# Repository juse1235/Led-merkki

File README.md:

# Salama
Sikin led salamaan ja Otitin led merkkiin koodi, piirilevy ja ohjeet

## Piirilevyt
### Mistä salama koostuu ja miten se toimii
Salaman mikrokontrolleri (mcu) ohjaa ledejä sytyttäen niitä yksi kerrallaan hyvin lyhyeksi aikaa.
Ledejä on 32 ja niille on 110 ohm etuvastukset.
Salamassa on myös 5v regulaattori joka pienentää 9v paristosta saatavan jännitteen viiteen volttiin.
Regulaattori vaatii toimiakseen kondensaattorit molemmille puolilleen.
Levyyn on myös suunniteltu kytkin, jolla voisi vaikka sammuttaa laitteen tai toimittaa muuta toiminnallisuutta, mutta näitä ei ole koodissa toteutettu vielä.
Kuusipinninen liitin on ohjelmointia varten ja sitä kautta ohjelma siirretääm mikrokontrollerille.

### Osaluettelo
  * 1 kpl  ATtiny861a SOIC
  * 32 kpl sininen 3 mm diffusoitu led
  * 4 kpl  110 Ohm 1206 smd-vastus
  * 2 kpl  10 µF tantaalikondensaattori smd (paketti?)
  * 1 kpl  Texas Instruments LP2981AIM5-5.0/NOPB Regulaattori sot23-5
  * 1 kpl  palautuva kytkin (tyyppi?)
  * 1 kpl  9v-paristolle paristoliitin
  * 1 kpl  kuusi pinniä pitkän piikkiriman
  
  lisäksi tarvitset:
  * kaksinapaista johtoa paristoliittimelle
  * kuumaliimaa
  * haalarimerkin :-)
  
### Piirikaavio

1. Läpiviennit
  Kaksipuoleisessa levyssä läpiviennit kuljettavat sähkön levyn puolelta toiselle.

  Mikäli olet saanut levyn yliopiston piirilevypajalta, siinä on luultavasti läpiviennit ja voit ohittaa tämän vaiheen.
  Jos piirilevy on syövytetty elektroniikkakerhon piirilevypajalla siinä ei ole läpivientejä ja ne täytyy juottaa itse.
  Juota siis johdon pätkä kuvassa oleviin reikiin molemmilta puolilta ja katkaise lopuksi mahdollisimman matalaksi.

  Levyn takapuoli. Tältä puolelta näkee mihin juotetaan läpiviennit.

2. Vastukset
  Levylle tulee neljä kappaletta 110 ohm vastuksia. Vastukset on merkattu kuviin tunnisteilla R1,R2,R3,R4.

  Pintaliitosvastus on helpoin juottaa siten, että juottaa vähän tinaa ensin piirilevyn toiselle pädille ja sitten vastus    siirretään oikealle paikalle, pidetään paikallaan painamalla jollain lämpöä kestävällä työkalulla ja painetaan kolvilla kunnes tina sulaa. Sitten voit juottaa toisen pädin normaalisti.
  
  Piirilevyn komponenttipuoli

  ##### Otit

  TODO: tähän vois panna kuvan kasatusta levystä
  
3. Regulaattori
   Regulaattori kannattaa juottaa ensin, koska se on ahtaassa kolossa. Regulaattorin juottamisessa täytyy myös olla huolellinen, ettei synny oikosulkuja.
   
4. Mikrokontrolleri
Mikrokontrollerissa polariteetti on merkitty lovella kuvassa ja lovella tai pisteellä itse komponentissa.

5. Kondensaattorit
  Tantaalikondensaattorissa polariteetti on merkitty viivalla joka tarkoitta positiivista puolta. Piirilevylle on piirretty paikat neljälle konkalle, kytke kuitenkin vain kaksi C3 ja C4.
  
6. Ohjelmointiliitin
  Juota pätkä piikkirimaa vaakatasoon. Liitin on kuvassa merkitty P1 ja siihen tulee kuusi pinniä.
  TODO: Kuva aiheesta selventäisi..

7. Kytkin
  Tällä hetkellä kytkimelle ei ole ohjelmoitu toiminnallisuutta, mutta sen juottaminen on niin pieni vaiva että se kannattanee kuitenkin tehdä. Kytkin siis asennetaan ylösalaisin niin että kytkimen hattu on levyn tasolla. Tarkoitus on siis että haalarimerkin läpi sitä olisi helppo painaa, mutta kuitenkin sitä ei tulisi vahingossa painettua.
  TODO: Lissää kuvia..
  
8. Ledit
  Ledien juottamisessa on suurin työmaa merkin valmistuksessa. Työtä aiheuttaa lähinnä ledin painaminen merkistä läpi.
  Ensin pitää huomioida polariteetti. Jos olet nähnyt paljon vaivaa että olet laittanut ledit miten sattuu niin voipi harmittaa..
  
  Elektroniikkakerholla on hankittu yleensä mahdollisimman edullisia ledejä joten voisi olla hyvä ennen juottamista testata ledit virtalähteellä. 
  
  Ledien jalat täytyy teroittaa leikkaamalla ne sivuleikkurilla mahdollisimman viistosti, niin että niistä tulee mahdollisimman terävät merkin läpi painamista varten. Leikkaa myös jalat reilusti eri mittaisiksi. Ne on helpompi painaa lapi yksi kerrallaan pihdeillä.
  
  Salaman ylä ja alapäässä on kaksi lediä piirretty niin lähellä toisiaan, että ledejä olisi hyvä vähän viilata jotta ne saa osoittamaan suoraan. (Aikaisemmassa leiskassa ledeillä oli tarpeeksi etäisyyttä mutta ne eivät pysyneet linjassa niin piirsin näin :-) )
  
  TODO: KUVA!!!
  
  Haalarimerkki kannattaa tässä vaiheessa kiinnittää ylimmän ja alimman ledin reistä johtimella kiinni oikealle kohdalle, helpottaa kasaamista. Itse olen kokenut käteväksi työmenetelmäksi että painan johtimen piirilevyn puolelta läpi ja sitten lämmitän sitä merkin puolelta niin että merkkiin sulaa/palaa pieni piste, josta sitten tietää mistä kohdasta ledin jalka kannattaa painaa läpi.

8. Virtajohto
  Virtajohto kannattaa liittää viimeisenä, koska se hankaloittaa levyn käsittelyä. Mitoita virtajohdon pituus niin, että se riittää taskuun missä aiot paristoa säilyttää paikasta johon merkin aiot ommella.
Johdon toiseen päähän juotetaan 9v-paristolle paristoliitin. Elekerholla on ollut huonoja paristoliittimiä joiden johdot ovat katkeilleet herkästi, joten liitin kannattaa ehkä purkaa, poistaa alkuperäiset johdot ja juottaa uusi johto tilalle. Paristoliitin suojataan kuumaliimalla.

  Kiinnitä huomiota polariteettiin. Salamaan ei ole suunniteltu suojaa väärinpäinkytkemisen varalta ja regulaattori palaa välittömästi kun näin tapahtuu. (Suojadiodin lisääminen olisi aika triviaalia) 
  TODO: Tähänki vois panna kuvan!

9. Ohjelmointi
  Ohjelmointiin on ohjeet jäljempänä.
  
10. Lopuksi kun on varmistettu että levy toimii oikein se kannattaa suojata kuumaliimalla niin että ledien terävät jalat peittyvät. Kytkin ja virtajohto kannattaa myös varmistaa hyvin. Merkkiä on vaikea korjata, kun se on kiinni haalareissa.

Todo: Syövytystä varten maskit. Sik maski saattaa löytyä vielä jostain. Otitille ei ole tehty vaan levyt jyrsittiin.

## Ohjelma

Ohjelma siirtyy levylle kätevästi käyttäen arduinoa ohjelmointilaitteena.

```
Salaman ohjelmointiliittimen pinnit keskeltä reunalle:

Nro:  Nimi:   Arduinon pinni (nano):

6:    Reset   10
5:    GND     GND
4:    VCC     VCC
3:    SCK     13
2:    MISO    12
1:    MOSI    11

Muista vetää arduinon Reset ylös. Ardu nollautuu kun sarjaliikenne alotetaan....
```

Src hakemistossa on lediportit_oikein.h ja lediportit_väärin.h tiedostot joista jompikumpi kopioidaan lediportit.h tiedoston päälle mikäli ledit on juotettu vastoin ohjetta. (TODO: nimet ovat ehkä väärin)

Koodin kääntämiseen ja ohjelman levylle siirtämiseen komennot ovat:

##### Linux ja Mac

```
// kääntäminen
avr-gcc -mmcu=attiny861 vilkutus.c salama.c -I./ -Os -DF_CPU=8000000UL  

// Fläsäys käyttäen arduino-isp:tä
avrdude -c avrisp -p t861 -B3 -P /dev/ttyUSB0 -b 19200 -U flash:w:a.out

// Fuse asetukset käyttäen arduino-isp:tä
avrdude -c avrisp -p t861 -B3 -P /dev/ttyUSB0 -b 19200 -U lfuse:w:0xe2:m -U hfuse:w:0xdf:m
```
##### Windows

```
// kääntäminen
avr-gcc -mmcu=attiny861 vilkutus.c salama.c -I./ -Os -DF_CPU=8000000UL

// Fläsäys käyttäen arduino-isp:tä
avrdude -C "C:\Program Files (x86)\Arduino\hardware\tools\avr\etc\avrdude.conf" -c avrisp -p t861 -B3 -P COM7 -b 19200 -U flash:w:a.out

// Fuse asetukset käyttäen arduino-isp:tä
avrdude -C "C:\Program Files (x86)\Arduino\hardware\tools\avr\etc\avrdude.conf" -c avrisp -p t861 -B3 -P COM7 -b 19200 -U lfuse:w:0xe2:m -U hfuse:w:0xdf:m
```
Windowsilla avrdude pitää olla ympäristömuuttujissa. Toinen vaihtoehto on ajaa komento "\Arduino\hardware\tools\avr\bin"-kansiossa.

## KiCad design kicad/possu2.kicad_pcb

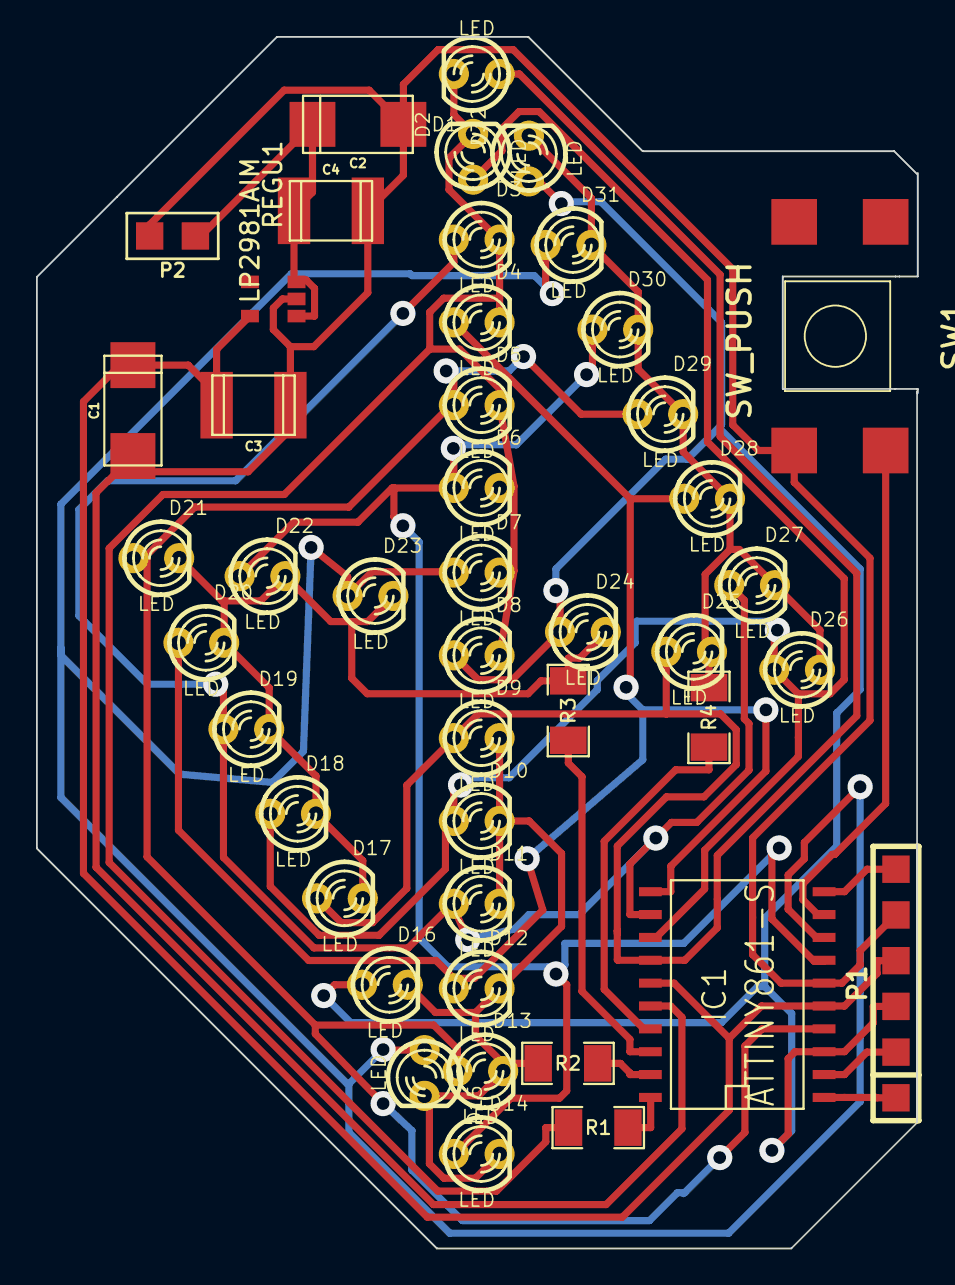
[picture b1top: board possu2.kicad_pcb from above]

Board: 2 copper layers, 48.9 x 67.3 mm, 45 parts (0 on the bottom side), 23 nets.

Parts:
C1, C2: CP1; c_tant_C
C3, C4: C; c_1812
D1, D2, D3, D4, D5, D6, D7, D8, D9, D10, D11, D12, D13, D14, D15, D16, D17, D18, D19, D20, D21, D22, D23, D24, D25, D26, D27, D28, D29, D30, D31, D32: LED; SalamaLED
IC1: ATTINY861-S; SO20L
P1: CONN_6; Ohjelmointiliitin
P2: CONN_2; Salama_virta
R1, R2, R3, R4: R; SM1206
REGU1: LP2981AIM; LM2981AIM
SW1: SW_PUSH; SalamaNAppi

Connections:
unnamed: IC1.18, R3.1
unnamed: IC1.19, R2.1
unnamed: IC1.20, R1.1
unnamed: IC1.2, P1.2
unnamed: IC1.10, P1.6
unnamed: IC1.9, SW1.2
unnamed: IC1.1, P1.1
unnamed: IC1.17, R4.1
unnamed: D1.1, D9.1, D17.1, D25.1, IC1.14
unnamed: D2.1, D10.1, D18.1, D26.1, IC1.13
unnamed: D6.1, D14.1, D22.1, D30.1, IC1.7
unnamed: D7.1, D15.1, D23.1, D31.1, IC1.8
unnamed: D8.1, D16.1, D24.1, D32.1, IC1.3, P1.3
unnamed: D3.1, D11.1, D19.1, D27.1, IC1.12
unnamed: D4.1, D12.1, D20.1, D28.1, IC1.11
unnamed: D5.1, D13.1, D21.1, D29.1, IC1.4
unnamed: D9.2, D10.2, D11.2, D12.2, D13.2, D14.2, D15.2, D16.2, R2.2
unnamed: C1.1, C3.1, IC1.5, IC1.15, P1.4, REGU1.5
unnamed: D25.2, D26.2, D27.2, D28.2, D29.2, D30.2, D31.2, D32.2, R4.2
unnamed: D17.2, D18.2, D19.2, D20.2, D21.2, D22.2, D23.2, D24.2, R3.2
unnamed: D1.2, D2.2, D3.2, D4.2, D5.2, D6.2, D7.2, D8.2, R1.2
unnamed: C2.1, C4.2, P2.1, REGU1.1, REGU1.3
unnamed: C1.2, C2.2, C3.2, C4.1, IC1.6, IC1.16, P1.5, P2.2, REGU1.2, SW1.1

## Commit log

2017-09-09 Siirsin kamat tänne
2017-09-09 Kuvia dokkariin
2017-09-09 Päivittelin ohjetta
2017-09-09 Lisäsin osaluettelon
2017-09-11 C3 and C4 polarity markings
    Clearer marks for C3 & C4 polarity
2025-09-14 Added Kicad project files
